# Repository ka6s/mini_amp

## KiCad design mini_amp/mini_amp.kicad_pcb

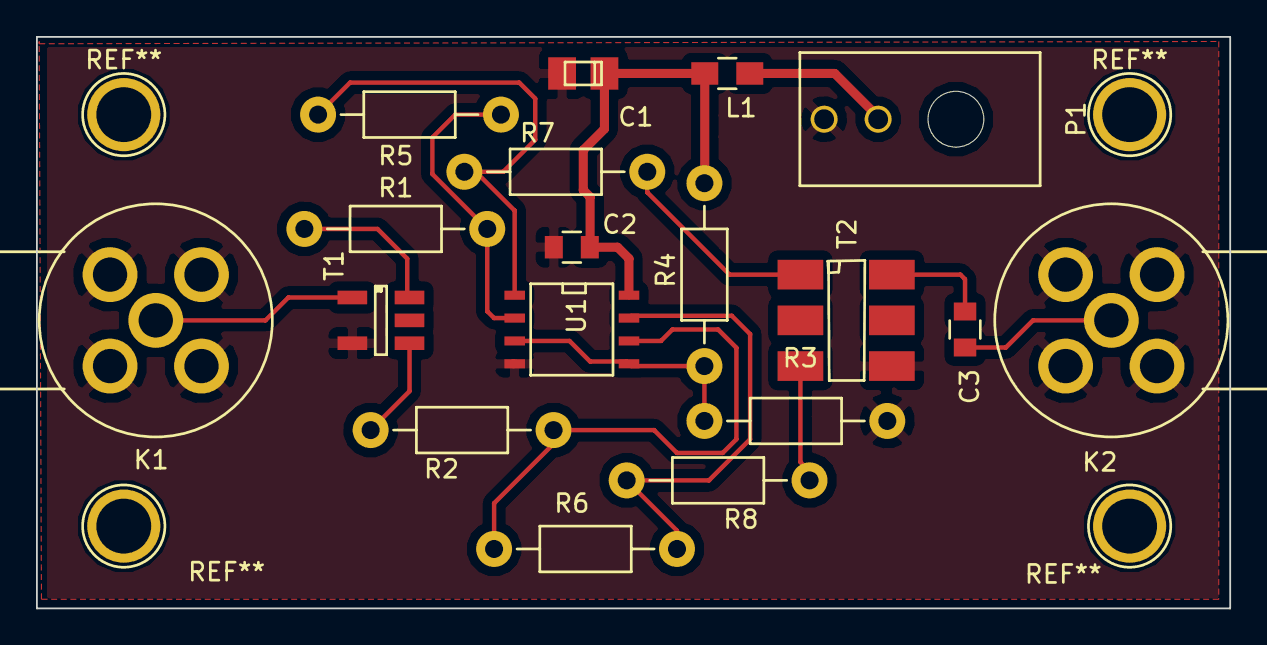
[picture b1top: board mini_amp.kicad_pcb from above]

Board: 2 copper layers, 66.3 x 31.8 mm, 18 parts (0 on the bottom side), 14 nets.

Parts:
C1: 10 uF/16V; TantalC_SizeR_EIA-2012
C2, C3: 100 nF; C_0805
K1, K2: SMA F R/A; SMA_F_RA
L1: Ferrite; C_0805_HandSoldering
P1: CONN_01X02; Connector_Microfit3_Header_02x01_Angled_43045-020x
R1, R2: 100; Resistor_Horizontal_RM10mm
R3, R4, R5, R6: 1K; Resistor_Horizontal_RM10mm
R7, R8: 4R99; Resistor_Horizontal_RM10mm
T1: TC4-1T
T2: ADT1.5-1
U1: OPA26741C; SOIC-8-N

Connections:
+12V: L1.2, P1.1
GND: C1.2, C2.2, K1.2, K1.3, K1.4, K1.5, K2.2, K2.3, K2.4, K2.5, P1.2, R3.2, T1.4, T2.4, U1.4
unnamed: C1.1, C2.1, L1.1, R4.1, U1.8
unnamed: C3.1, K2.1
unnamed: C3.2, T2.6
unnamed: R1.1, R5.2, U1.2
unnamed: R1.2, T1.1
unnamed: R2.1, R6.2, U1.6
unnamed: R2.2, T1.3
unnamed: R3.1, R4.2, U1.3, U1.5
unnamed: R5.1, R7.1, U1.1
unnamed: R6.1, R8.2, U1.7
unnamed: R7.2, T2.1
unnamed: R8.1, T2.3

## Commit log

2016-11-12 Push the rest of the directory up
